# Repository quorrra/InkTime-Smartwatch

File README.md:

# InkTime — Open Source Smartwatch

InkTime is a low-cost, open-source smartwatch designed for extreme battery life and hackability.  
It features a **1.54" E-Paper display**, a **Nordic nRF52840 BLE SoC**, and a high-efficiency power system.

---

## 1) Block Diagram

The hardware architecture revolves around the nRF52840 MCU and a power system designed for month-long battery life.

````text
[ USB Type-C ]                              [ LiPo Battery (250mAh) ]
                 | 5V VBUS                                      |
                 v                                              |
          +---------------+                                     |
          |    BQ25180    | BAT                                 |
          | (Charger IC)  |<------------------------------------+
          +---------------+                                     v
                 | VSYS                                 +---------------+
                 v                                      |   MAX17048    |
          +---------------+                             | (Fuel Gauge)  |
          |    RT6160     |                             +---------------+
          | (Buck-Boost)  |                                     ^
          +---------------+                                     |
                 | 3.3V System Rail (VDD_3V3)                   |
                 |                                              |
 +---------------+----------------------------------------------+-----+
 |               |                                              |     |
 |               v                                              |     |
 |        +-------------+         I2C Bus                       |     |
 |        |  nRF52840   |<======================================+     |
 |        |    MCU      |                                             |
 |        |             |=== I2C ===> [ BMA423 Accelerometer ]        |
 |        |             |=== I2C ===> [ DRV2605L Driver ]-->[ Motor ] |
 |        |             |=== SPI ===> [ 1.54" E-paper Display ]       |
 |        |             |                       ^                      |
 |        |             |-- GPIO (Gate)         | VEPD (Switched Pwr) |
 |        +-------------+      |                |                      |
 |          ^  ^  ^  |         v                |                      |
 |          |  |  |  | +---------------+        |                      |
 +---------(|--|--|)-+-|  PFET Switch  |--------+                      |
            |  |  |  | +---------------+                               |
 [Up]-------+  |  |  |                                                 |
           [Down] |  +--- [ 2.4GHz Antenna ] - - BLE - - [ Companion Phone ]
                  |
              [Enter/Esc]
````

---

## 2) Bill of Materials (BOM)

All components are selected from the JLC Parts library for easy manufacturing and assembly.

| RefDes | Component      | Description               | JLC Part # | Datasheet |
|--------|----------------|---------------------------|------------|-----------|
| U1     | nRF52840       | BLE SoC, Cortex-M4F       | [C137156](https://jlcpcb.com/partdetail/C190794)    | BLE, Native USB      |
| IC1    | BQ25180        | Li-Ion Charger            | [C2907455](https://jlcpcb.com/partdetail/C3682423)   |Safe USB power-path     |
| IC9    | RT6160AWSC     | Buck-Boost Converter      | [C2834376](https://jlcpcb.com/partdetail/C7065276)   | 3.3V System Rail      |
| U3     | MAX17048G      | I2C Fuel Gauge            | [C146603](https://jlcpcb.com/partdetail/C2682616)    | 1-Cell Battery Monitor      |
| IC3    | BMA423         | 3-axis Accelerometer      | [C224345](https://jlcpcb.com/partdetail/C5242966)    | Embedded pedometer      |
| IC4    | DRV2605YZFR    | Haptic Driver             | [C146312](https://jlcpcb.com/partdetail/C527464)    | For ERM motor     |
| J4     | KH-TYPE-C-16P  | USB-C Connector           | [C319148](https://jlcpcb.com/partdetail/C7528806)    |High-side power switch    |

---

## 3) Hardware Functionality

### 3.1 Power Management System
- The watch is powered by a **250mAh LiPo battery**.
- **Charging:** BQ25180 handles USB charging (5V VBUS) and system power-path management.
- **Regulation:** RT6160 buck-boost ensures a stable **3.3V rail** even when battery voltage drops below 3.3V.
- **Fuel Gauge:** MAX17048 uses ModelGauge for accurate **SoC (%)** via I2C, without a sense resistor.

### 3.2 Processing & Connectivity
The **nRF52840** is the central processor, running BLE for smartphone notifications and controlling peripherals over I2C/SPI.

### 3.3 Display & Haptics
- **E-Paper Display:** 1.54", ultra-low power (0W image retention), controlled via SPI.
- **Haptics:** DRV2605 drives an LRA motor for tactile alerts and alarms.

---

## 4) nRF52840 Pin Mapping

| Pin   | Signal Name | Interface  | Function |
|-------|-------------|------------|----------|
| P0.13 | SW_UP       | GPIO (In)  | Up navigation button |
| P0.14 | SW_ENT      | GPIO (In)  | Enter/Select button |
| P1.02 | SW_DN       | GPIO (In)  | Down navigation button |
| P0.08 | I2C_SDA     | I2C Data   | Shared SDA (IMU, Charger, Gauge, Haptic) |
| P1.09 | I2C_SCL     | I2C Clock  | Shared SCL (IMU, Charger, Gauge, Haptic) |
| P0.20 | EPD_RESET   | GPIO (Out) | Display hardware reset |
| P0.22 | EPD_BUSY    | GPIO (In)  | Display status pin |
| P0.12 | HAPTIC_EN   | GPIO (Out) | Enable for DRV2605 haptic driver |
| P0.01 | EPD_DC      | GPIO (Out) | Data/Command selector for E-paper |
| P0.03 | EPD_CS      | SPI CS     | Chip select for E-paper display |

---

## 5) Design & Manufacturing Details

### 5.1 PCB Stackup & Constraints
- **Stackup:** 4-layer PCB (Top, GND Plane, Power Plane, Bottom)
- **Thickness:** 1.0 mm (wearable-friendly)
- **Antenna:** 2.4 GHz PCB antenna at board edge with ground clearance for BLE performance

### 5.2 Component Selection
- **Passives:**  
  - Resistors: 0201 SMD  
  - Capacitors ≤100nF: 0201  
  - Capacitors >100nF: 0402 (unless otherwise specified)
- **Placement:** All components on TOP layer

### 5.3 Routing Rules
- **Power traces** (VCC, VUSB, VBUS, 3V3): 0.3 mm
- **Signal traces:** minimum 0.15 mm
- **Grounding:** solid Layer 2 GND plane + via stitching for EMI/thermal performance

---

## 6) Design Log & Decisions

- **4-layer decision:** moved from 2 to 4 layers to route the 24-pin E-paper connector.
- **GND plane:** Layer 2 kept continuous for RF reference and improved signal integrity.
- **Mechanical fit:** verified in 3D enclosure model (USB-C and buttons aligned with housing).

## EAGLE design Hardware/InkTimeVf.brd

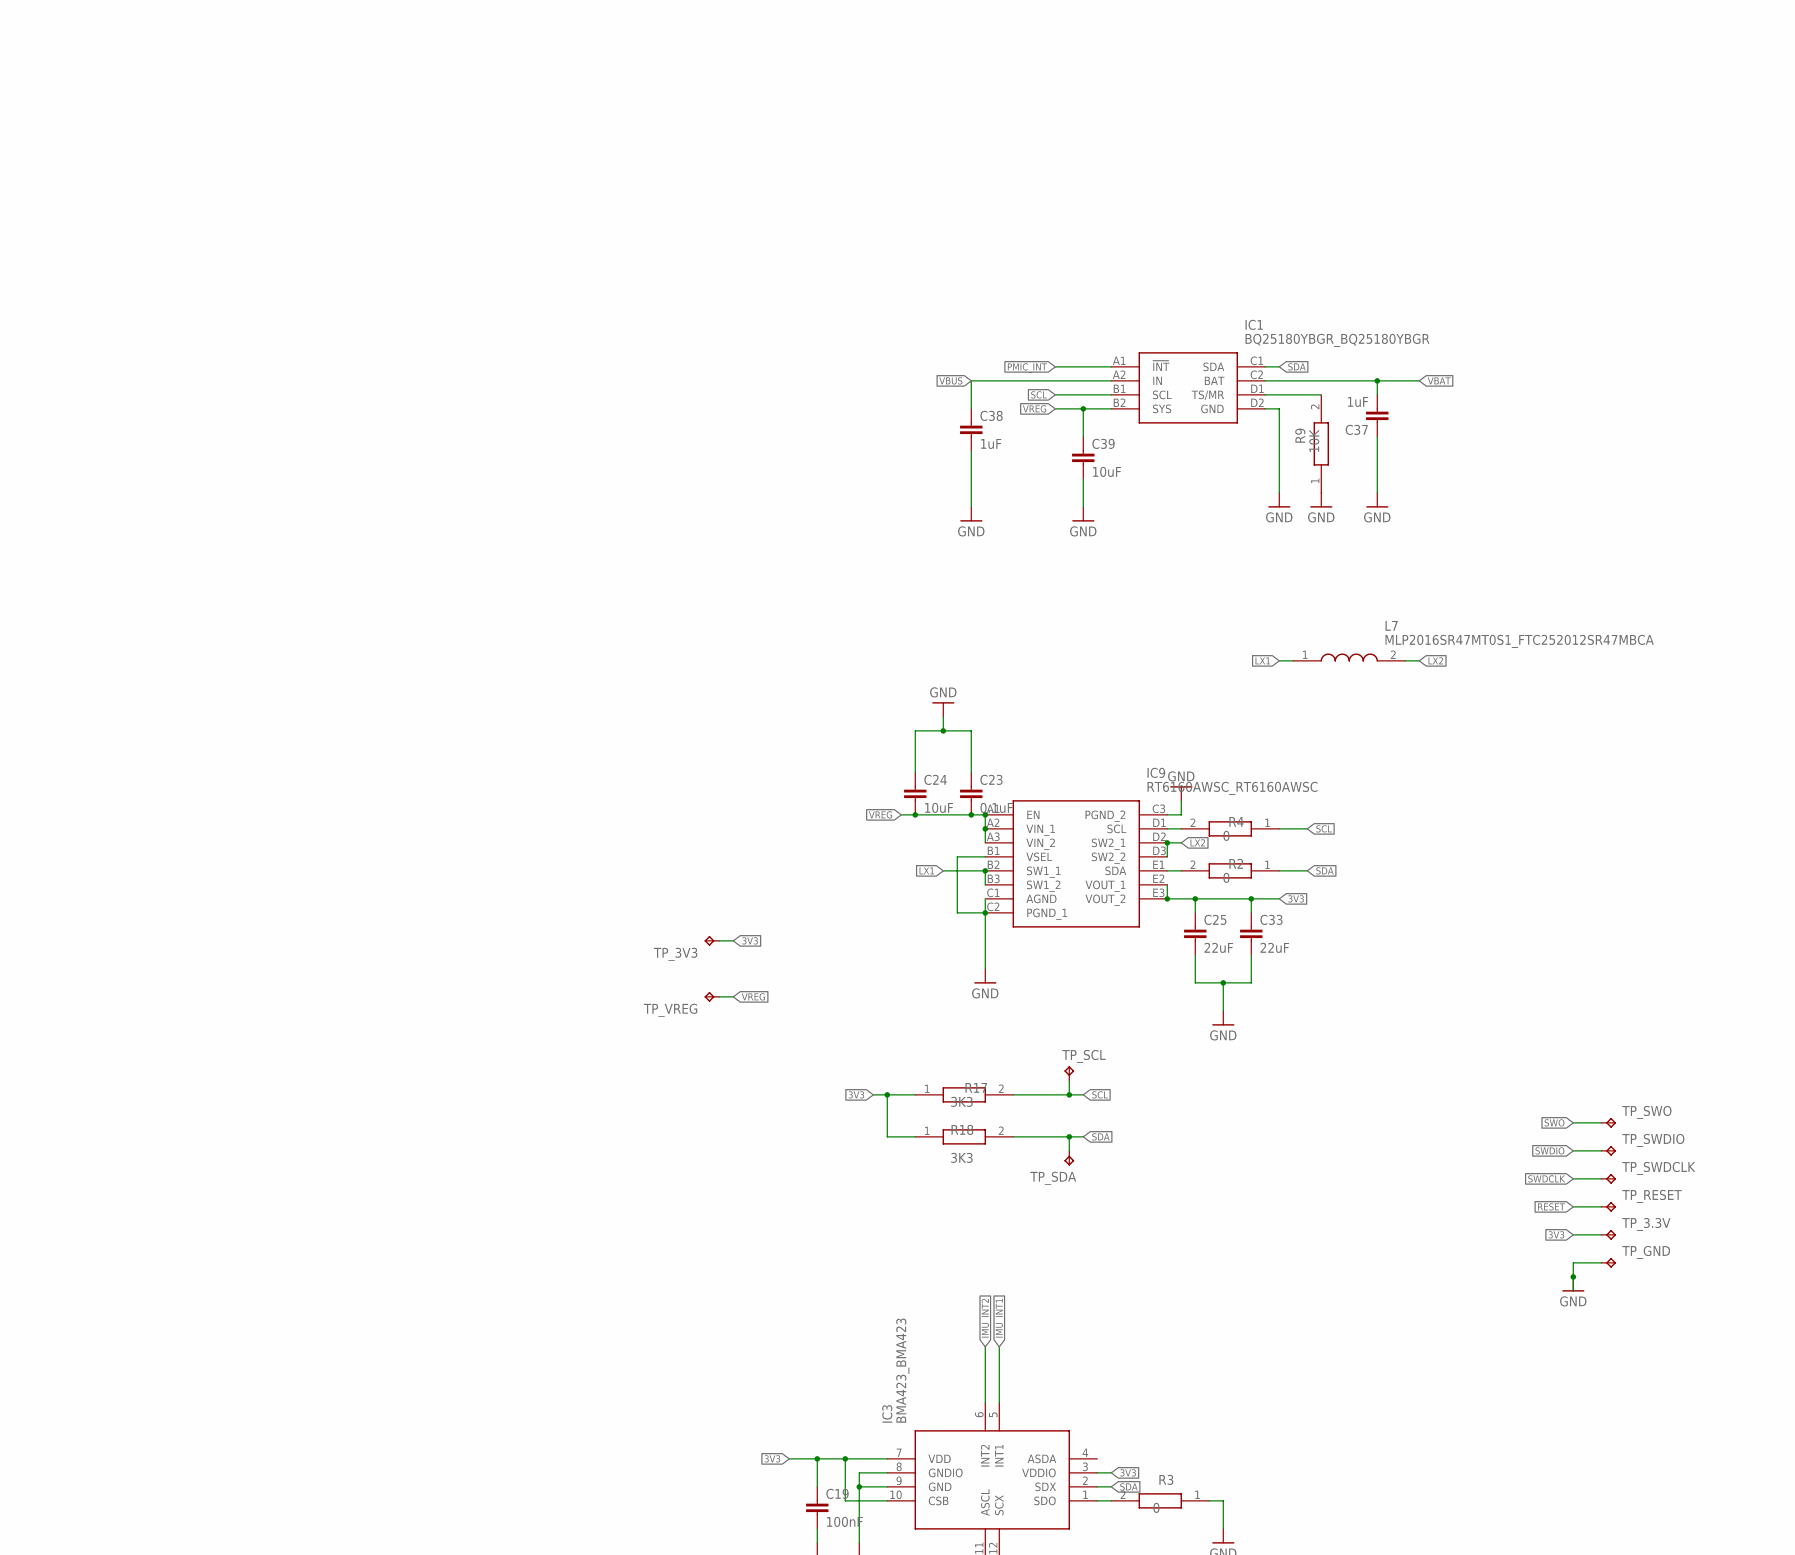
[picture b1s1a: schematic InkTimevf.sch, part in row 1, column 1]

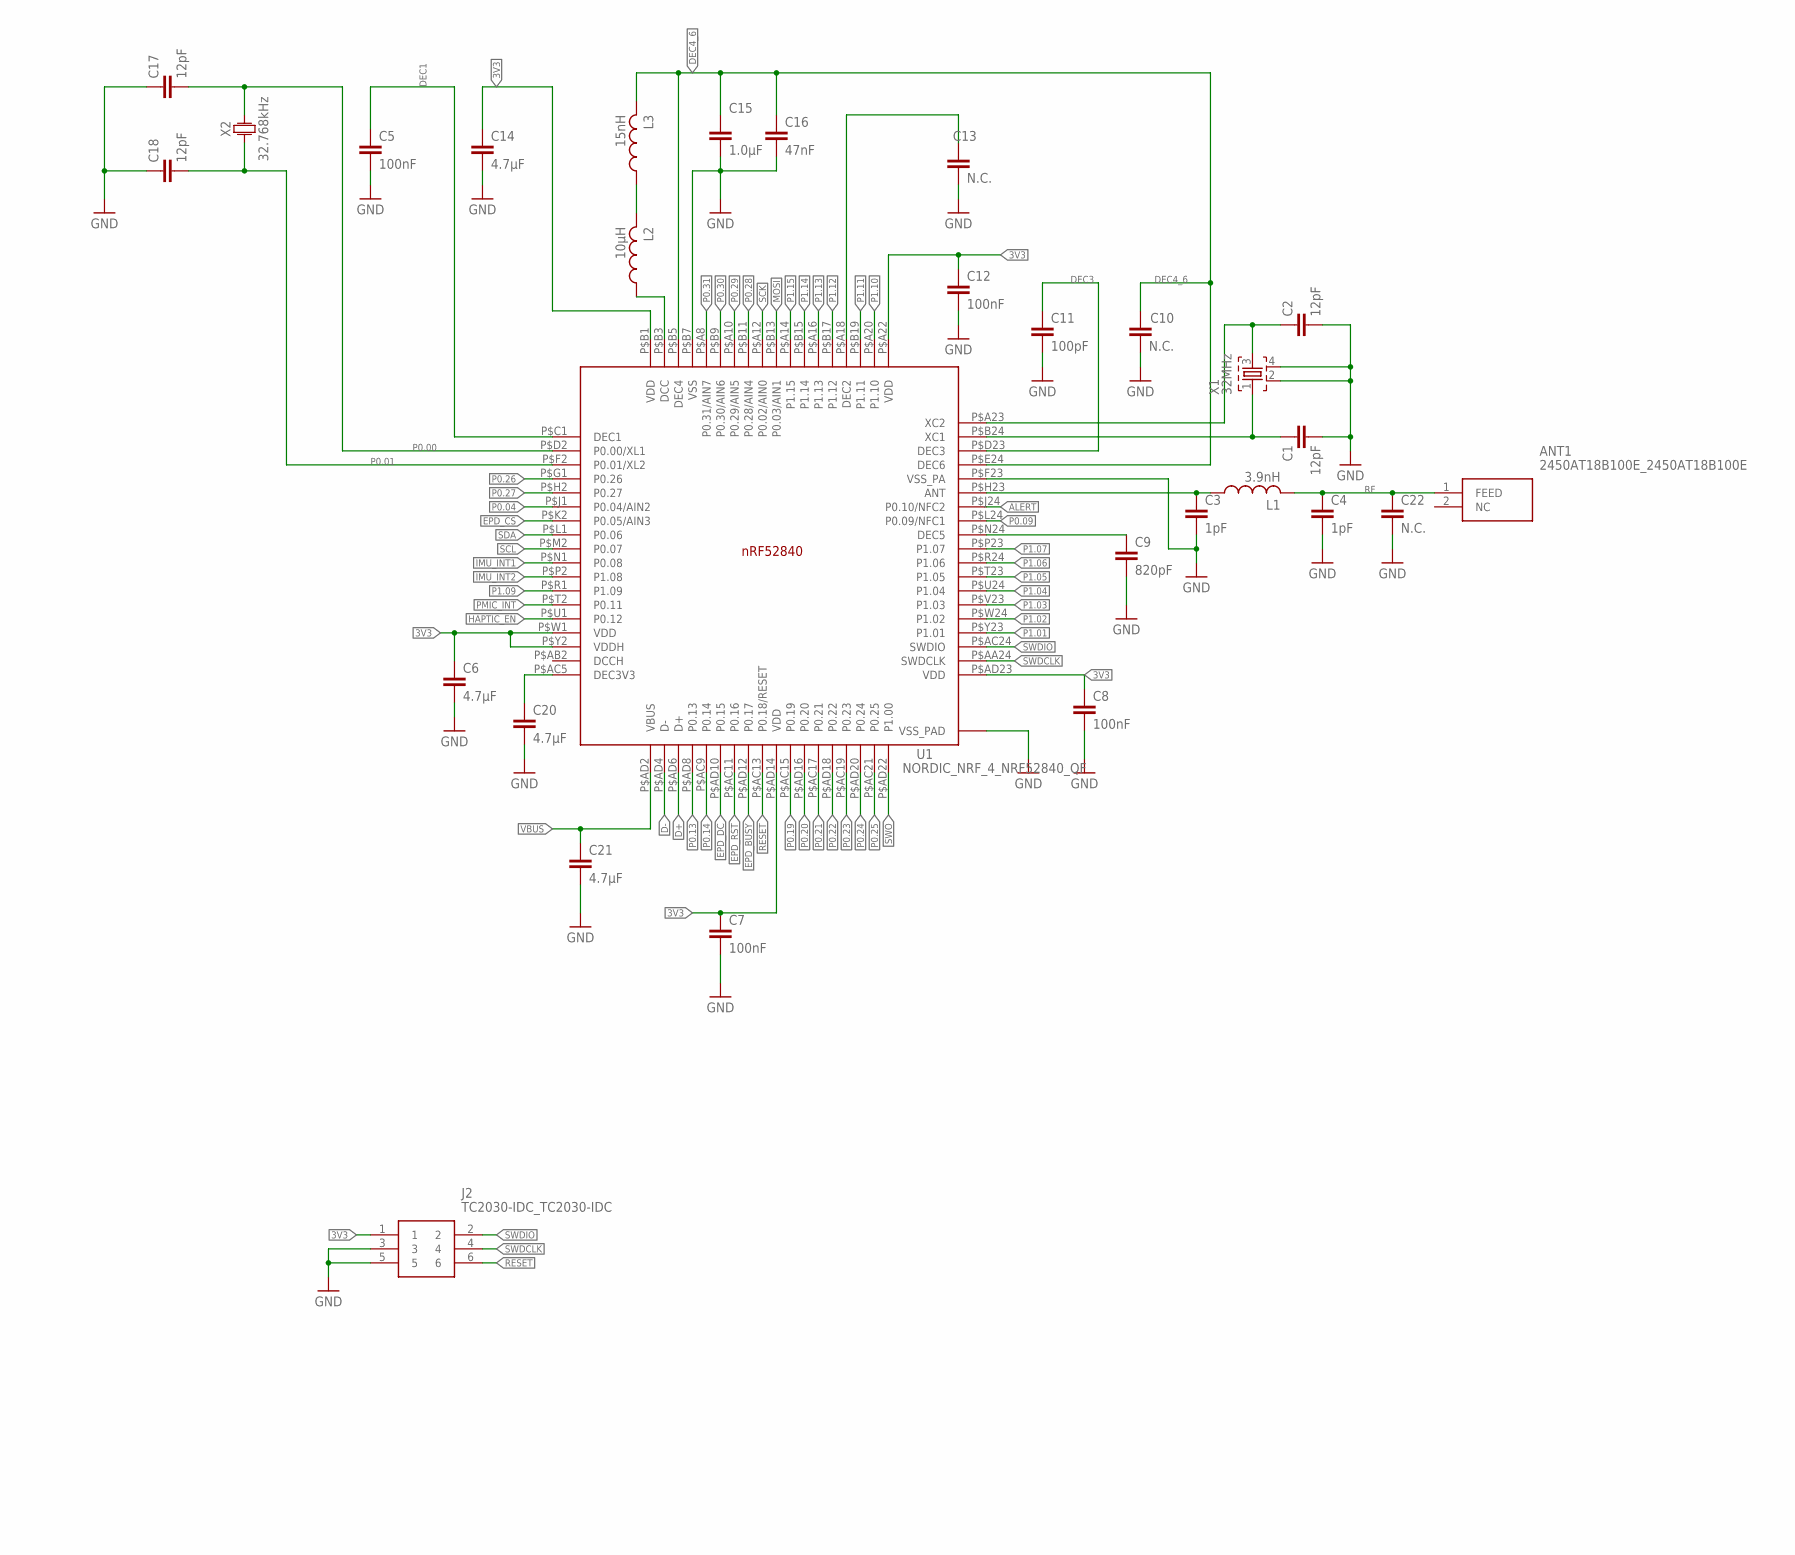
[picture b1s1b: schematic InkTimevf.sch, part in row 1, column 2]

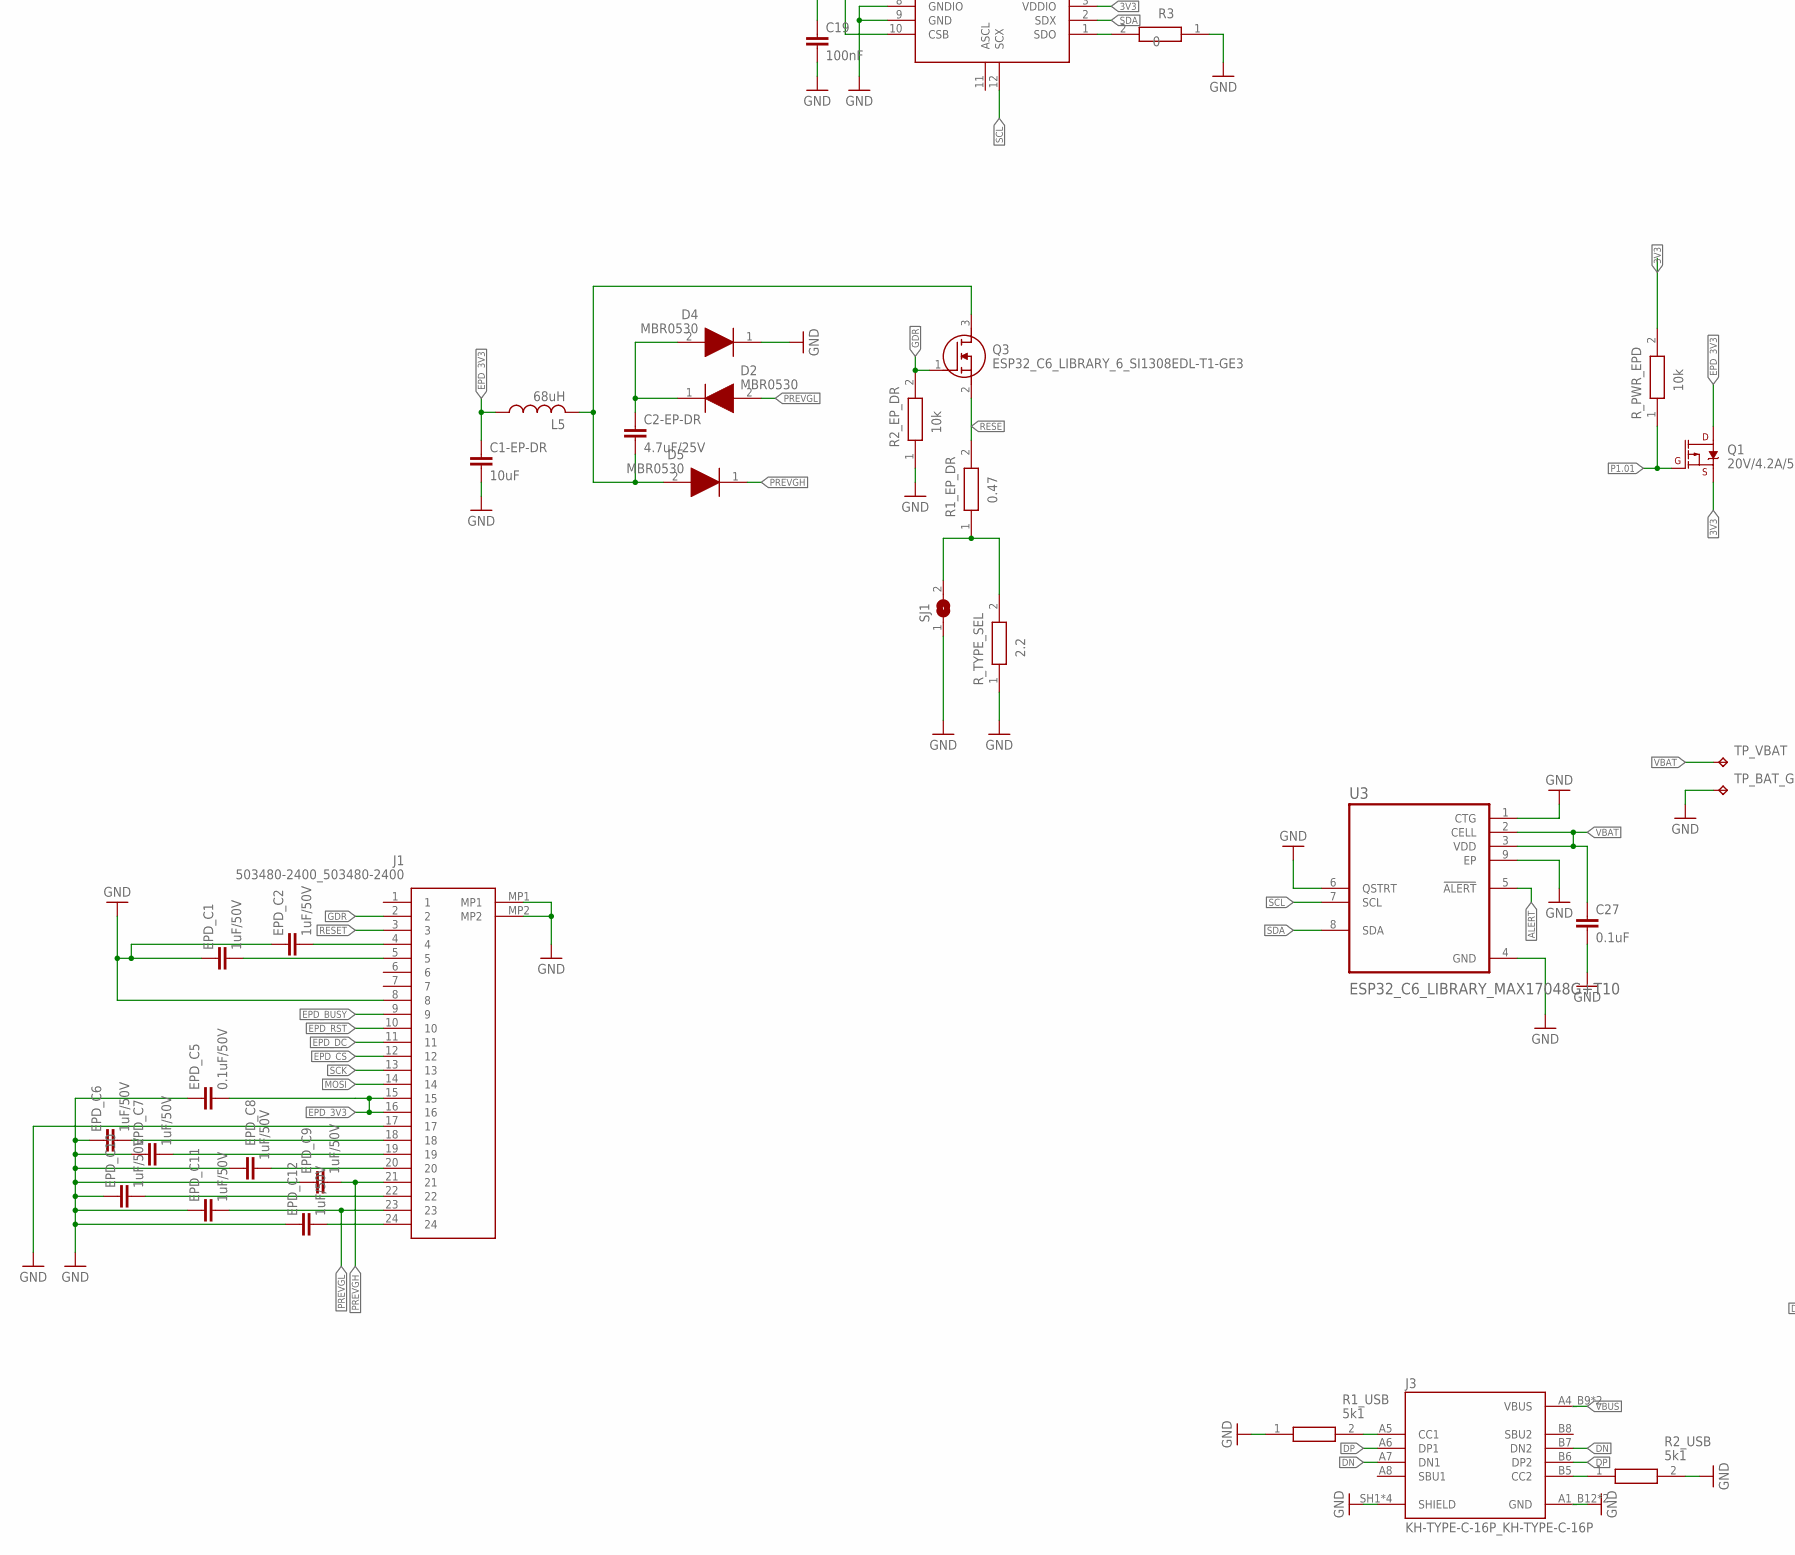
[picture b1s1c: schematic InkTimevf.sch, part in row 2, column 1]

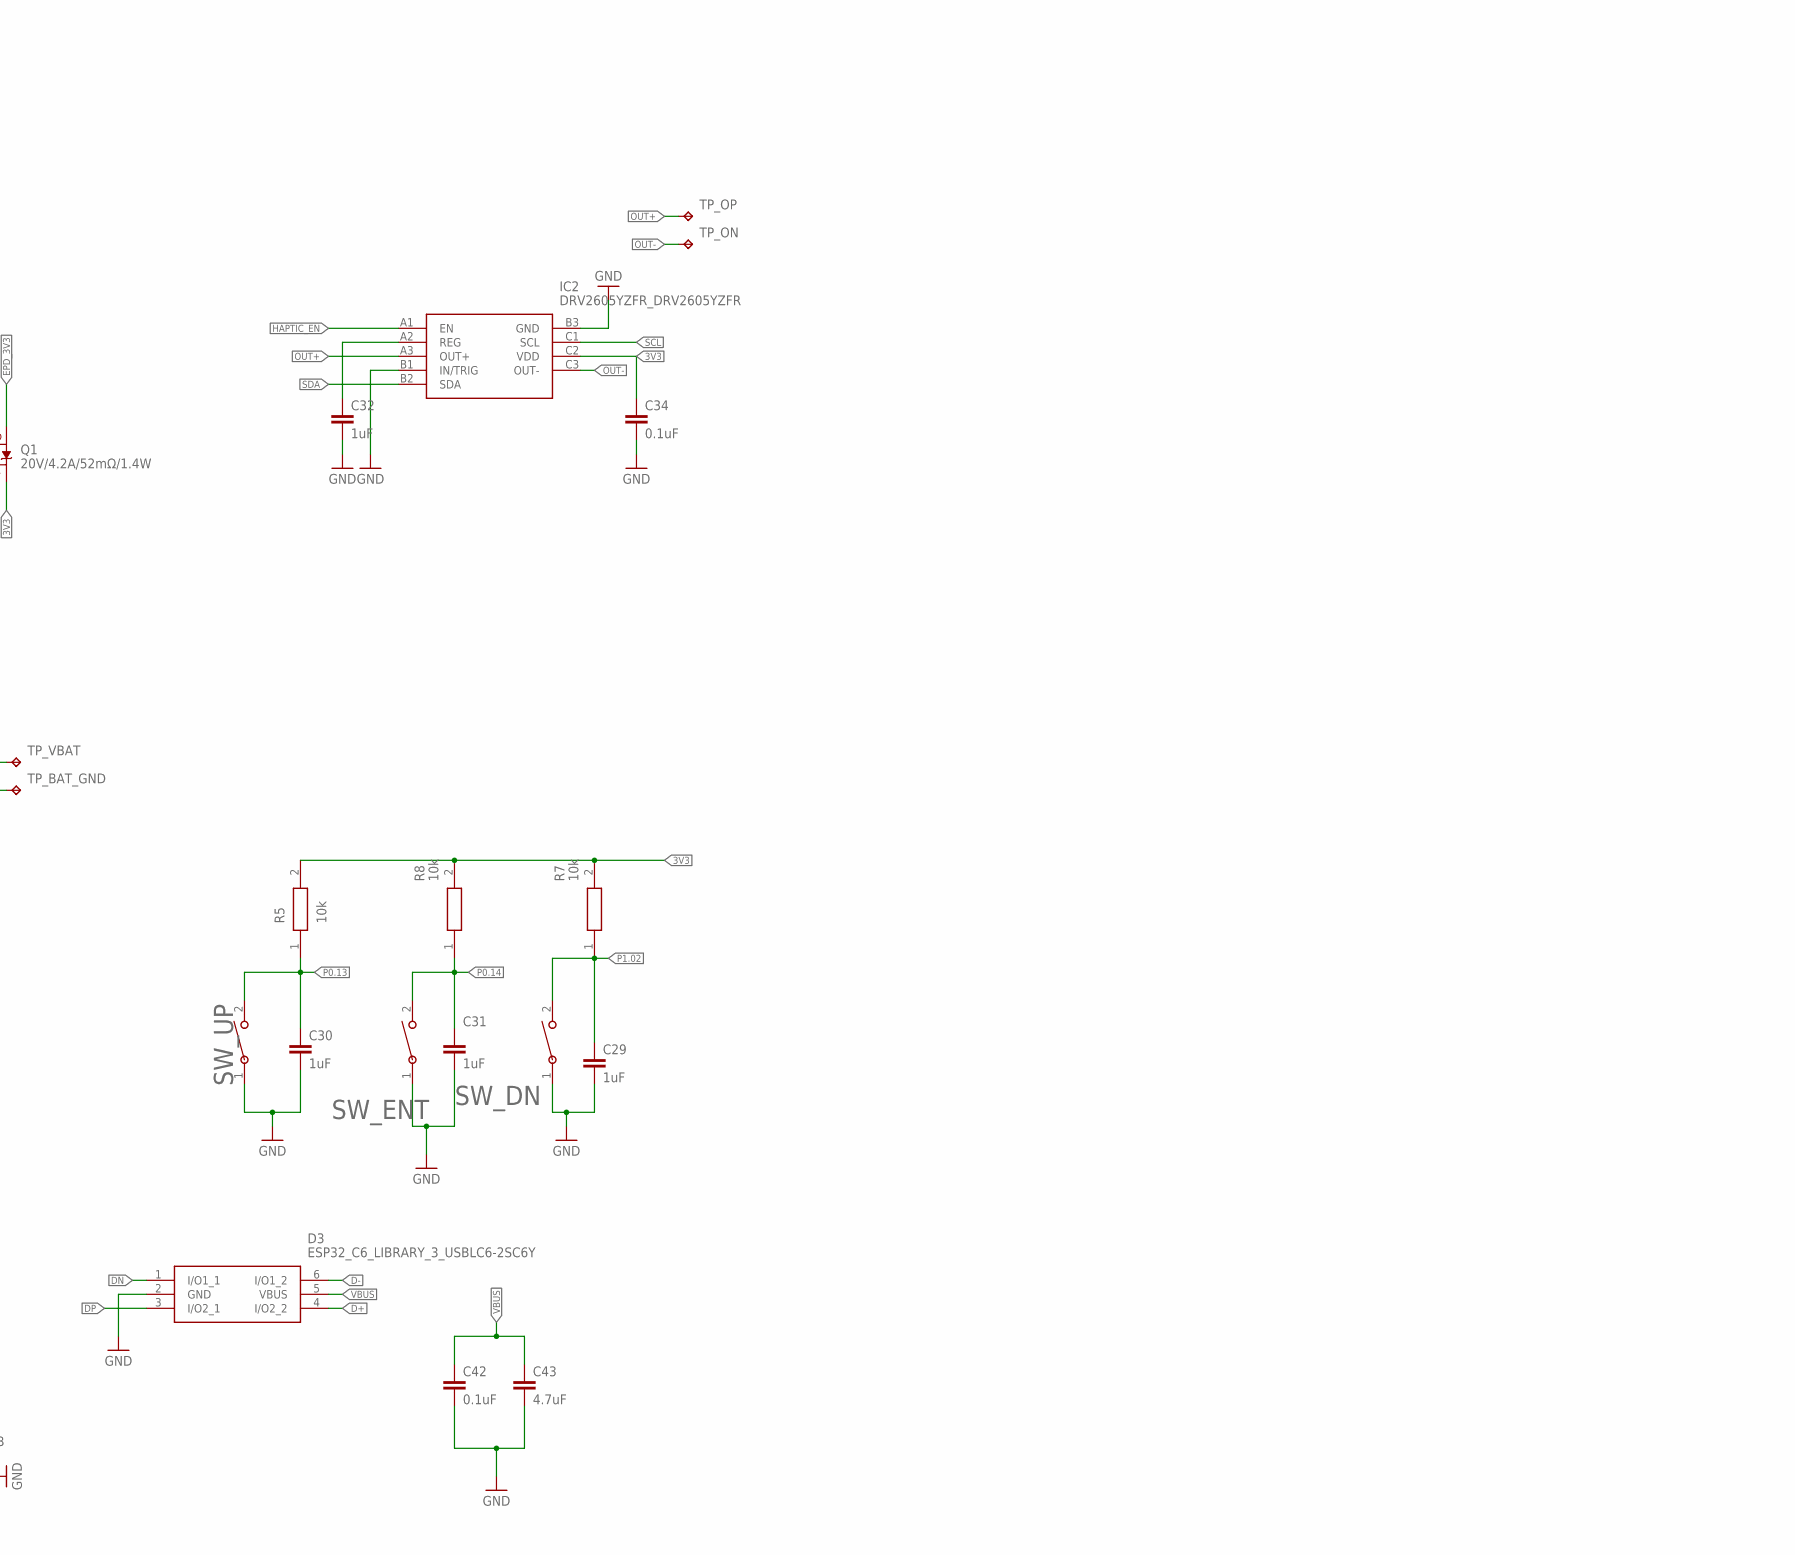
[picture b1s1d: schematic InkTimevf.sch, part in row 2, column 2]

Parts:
ANT1: 2450AT18B100E_2450AT18B100E; 2450AT18B100E_ANTC3216X140N
C1, C2, C17, C18: 12pF; NORDIC_NRF_3_RESC0201_L
C1-EP-DR, C24, C39: 10uF; ESP32_C6_LIBRARY_1_ESP32_WROVER_EAGLE-LTSPICE_C0402
C2-EP-DR: 4.7uF/25V; ESP32_C6_LIBRARY_1_ESP32_WROVER_EAGLE-LTSPICE_C0402
C3, C4: 1pF; NORDIC_NRF_3_RESC0201_L
C5, C7, C8, C12, C19: 100nF; NORDIC_NRF_3_RESC0201_L
C6, C14, C20, C21: 4.7µF; ESP32_C6_LIBRARY_1_ESP32_WROVER_EAGLE-LTSPICE_C0402
C9: 820pF; NORDIC_NRF_3_RESC0201_L
C10, C13, C22: N.C.; NORDIC_NRF_3_RESC0201_L
C11: 100pF; NORDIC_NRF_3_RESC0201_L
C15: 1.0µF; ESP32_C6_LIBRARY_1_ESP32_WROVER_EAGLE-LTSPICE_C0402
C16: 47nF; NORDIC_NRF_3_RESC0201_L
C23, C27, C34, C42: 0.1uF; NORDIC_NRF_3_RESC0201_L
C25, C33: 22uF; ESP32_C6_LIBRARY_1_ESP32_WROVER_EAGLE-LTSPICE_C0402
C29, C30, C31, C32, C37, C38: 1uF; ESP32_C6_LIBRARY_1_ESP32_WROVER_EAGLE-LTSPICE_C0402
C43: 4.7uF; ESP32_C6_LIBRARY_1_ESP32_WROVER_EAGLE-LTSPICE_C0402
D2, D4, D5: MBR0530; ESP32_C6_LIBRARY_5_SOD3716X135N
D3: ESP32_C6_LIBRARY_3_USBLC6-2SC6Y; ESP32_C6_LIBRARY_3_SOT95P280X145-6N
EPD_C1, EPD_C2, EPD_C6, EPD_C7, EPD_C8, EPD_C9, EPD_C10, EPD_C11, EPD_C12: 1uF/50V; ESP32_C6_LIBRARY_1_ESP32_WROVER_EAGLE-LTSPICE_C0402
EPD_C5: 0.1uF/50V; NORDIC_NRF_3_RESC0201_L
IC1: BQ25180YBGR_BQ25180YBGR; BQ25180YBGR_BGA8C40P2X4_100X155X50
IC2: DRV2605YZFR_DRV2605YZFR; DRV2605YZFR_BGA9C50P3X3_144X144X62
IC3: BMA423_BMA423
IC9: RT6160AWSC_RT6160AWSC; RT6160AWSC_BGA15C40P3X5_140X230X60
J1: 503480-2400_503480-2400; 503480-2400_5034802400
J2: TC2030-IDC_TC2030-IDC; TC2030-IDC_TC2030IDC
J3: KH-TYPE-C-16P_KH-TYPE-C-16P; KH-TYPE-C-16P_KINGHELM_KH-TYPE-C-16P
L1: 3.9nH; NORDIC_NRF_2_RESC0402_L
L2: 10µH; NORDIC_NRF_2_RESC0402_L
L3: 15nH; NORDIC_NRF_2_RESC0402_L
L5: 68uH; NORDIC_NRF_2_RESC0402_L
L7: MLP2016SR47MT0S1_FTC252012SR47MBCA; MLP2016SR47MT0S1_INDC2016X100N
Q1: 20V/4.2A/52mΩ/1.4W; ESP32_C6_LIBRARY_4_ESP32_C6_LIBRARY_4_ESP32_C6_LIBRARY_4_ES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
Q3: ESP32_C6_LIBRARY_6_SI1308EDL-T1-GE3; ESP32_C6_LIBRARY_6_SOT65P210X110-3N
R1_EP_DR: 0.47; CPF0201D7K68C1_0201
R1_USB, R2_USB: 5k1; CPF0201D7K68C1_0201
R2, R4: 0; ERA-1AEB3401C_0201
R2_EP_DR, R5, R7, R8: 10k; CPF0201D7K68C1_0201
R3: 0; CPF0201D7K68C1_0201
R9: 10K; CPF0201D7K68C1_0201
R17, R18: 3K3; ERA-1AEB3401C_0201
R_PWR_EPD: 10k; ERA-1AEB3401C_0201
R_TYPE_SEL: 2.2; CPF0201D7K68C1_0201
SJ1: ESP32_C6_LIBRARY_7_JUMPER_SJ
SW_DN: 2025-10-22_07-23-44_LIBRARY_EVP-AKE31ASW_EVP-AKE3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; 2025-10-22_07-23-44_LIBRARY_SW_EVP-AKE31A_PAN
SW_ENT: 2025-10-22_07-23-44_LIBRARY_EVP-AKE31ASW_EVP-AKE3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; 2025-10-22_07-23-44_LIBRARY_SW_EVP-AKE31A_PAN
SW_UP: 2025-10-22_07-23-44_LIBRARY_EVP-AKE31ASW_EVP-AKE3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; 2025-10-22_07-23-44_LIBRARY_SW_EVP-AKE31A_PAN
TP_3.3V, TP_3V3: HECTOR_WATCH_1_TPTP20R; HECTOR_WATCH_1_TP20R
TP_BAT_GND: HECTOR_WATCH_1_TPTP20R; HECTOR_WATCH_1_TP20R
TP_GND: HECTOR_WATCH_1_TPTP20R; HECTOR_WATCH_1_TP20R
TP_ON: HECTOR_WATCH_1_TPTP20R; HECTOR_WATCH_1_TP20R
TP_OP: HECTOR_WATCH_1_TPTP20R; HECTOR_WATCH_1_TP20R
TP_RESET: HECTOR_WATCH_1_TPTP20R; HECTOR_WATCH_1_TP20R
TP_SCL: HECTOR_WATCH_1_TPTP20R; HECTOR_WATCH_1_TP20R
TP_SDA: HECTOR_WATCH_1_TPTP20R; HECTOR_WATCH_1_TP20R
TP_SWDCLK: HECTOR_WATCH_1_TPTP20R; HECTOR_WATCH_1_TP20R
TP_SWDIO: HECTOR_WATCH_1_TPTP20R; HECTOR_WATCH_1_TP20R
TP_SWO: HECTOR_WATCH_1_TPTP20R; HECTOR_WATCH_1_TP20R
TP_VBAT: HECTOR_WATCH_1_TPTP20R; HECTOR_WATCH_1_TP20R
TP_VREG: HECTOR_WATCH_1_TPTP20R; HECTOR_WATCH_1_TP20R
U1: NORDIC_NRF_4_NRF52840_QF; NORDIC_NRF_4_AQFN50P700X700X85_HS-74N
U3: ESP32_C6_LIBRARY_MAX17048G+T10; ESP32_C6_LIBRARY_SON50P200X200X80-9N
X1: 32MHz; NORDIC_NRF_BT-XTAL_2016_N
X2: 32.768kHz; XTAL330X1051X90N

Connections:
3V3: C6.1, C7.1, C8.1, C12.1, C14.1, C19.1, C25.1, C33.1, C34.1, IC2.C2 (VDD), IC3.3 (VDDIO), IC3.7 (VDD), IC3.10 (CSB), IC9.E2 (VOUT_1), IC9.E3 (VOUT_2), J2.1, Q1.2 (S), R5.2, R7.2, R8.2, R17.1, R18.1, R_PWR_EPD.2, TP_3.3V.TP, TP_3V3.TP, U1.P$A22 (VDD), U1.P$AD14 (VDD), U1.P$AD23 (VDD), U1.P$B1 (VDD), U1.P$W1 (VDD), U1.P$Y2 (VDDH)
ALERT: U1.P$J24 (P0.10/NFC2), U3.5 (!ALERT)
D+: D3.4 (I/O2_2), U1.P$AD6 (D+)
D-: D3.6 (I/O1_2), U1.P$AD4 (D-)
DEC1: C5.1, U1.P$C1 (DEC1)
DEC3: C11.1, U1.P$D23 (DEC3)
DEC4_6: C10.1, C15.1, C16.1, L3.2, U1.P$B5 (DEC4), U1.P$E24 (DEC6)
DN: D3.1 (I/O1_1), J3.A7 (DN1), J3.B7 (DN2)
DP: D3.3 (I/O2_1), J3.A6 (DP1), J3.B6 (DP2)
EPD_3V3: C1-EP-DR.1, EPD_C5.2, J1.15, J1.16, L5.1, Q1.3 (D)
EPD_BUSY: J1.9, U1.P$AD12 (P0.17)
EPD_CS: J1.12, U1.P$K2 (P0.05/AIN3)
EPD_DC: J1.11, U1.P$AD10 (P0.15)
EPD_RST: J1.10, U1.P$AC11 (P0.16)
GDR: J1.2, Q3.1 (G), R2_EP_DR.2
GND: C1.2, C1-EP-DR.2, C2.2, C3.2, C4.2, C5.2, C6.2, C7.2, C8.2, C9.2, C10.2, C11.2, C12.2, C13.2, C14.2, C15.2, C16.2, C17.1, C18.1, C19.2, C20.2, C21.2, C22.2, C23.1, C24.1, C25.2, C27.2, C29.2, C30.2, C31.2, C32.2, C33.2, C34.2, C37.1, C38.2, C39.2, C42.2, C43.2, D3.2 (GND), D4.1 (K), EPD_C1.1, EPD_C2.1, EPD_C5.1, EPD_C6.1, EPD_C7.1, EPD_C8.1, EPD_C9.1, EPD_C10.1, EPD_C11.1, EPD_C12.1, IC1.D2 (GND), IC2.B1 (IN/TRIG), IC2.B3 (GND), IC3.8 (GNDIO), IC3.9 (GND), IC9.B1 (VSEL), IC9.C1 (AGND), IC9.C2 (PGND_1), IC9.C3 (PGND_2), J1.8, J1.17, J1.MP1, J1.MP2, J2.3, J2.5, J3.A1_B12 (GND), J3.A12_B1 (GND), J3.SH1 (SHIELD), J3.SH2 (SHIELD), J3.SH3 (SHIELD), J3.SH4 (SHIELD), R1_USB.1, R2_EP_DR.1, R2_USB.2, R3.1, R9.1, R_TYPE_SEL.1, SJ1.1, SW_DN.1, SW_ENT.1, SW_UP.1, TP_BAT_GND.TP, TP_GND.TP, U1.P$74 (VSS_PAD), U1.P$75 (VSS_PAD), U1.P$76 (VSS_PAD), U1.P$77 (VSS_PAD), U1.P$78 (VSS_PAD), U1.P$79 (VSS_PAD), U1.P$80 (VSS_PAD), U1.P$81 (VSS_PAD), U1.P$82 (VSS_PAD), U1.P$83 (VSS_PAD), U1.P$84 (VSS_PAD), U1.P$85 (VSS_PAD), U1.P$86 (VSS_PAD), U1.P$87 (VSS_PAD), U1.P$88 (VSS_PAD), U1.P$89 (VSS_PAD), U1.P$90 (VSS_PAD), U1.P$B7 (VSS), U1.P$F23 (VSS_PA), U3.1 (CTG), U3.4 (GND), U3.6 (QSTRT), U3.9 (EP), X1.2, X1.4
HAPTIC_EN: IC2.A1 (EN), U1.P$U1 (P0.12)
IMU_INT1: IC3.5 (INT1), U1.P$N1 (P0.08)
IMU_INT2: IC3.6 (INT2), U1.P$P2 (P1.08)
LX1: IC9.B2 (SW1_1), IC9.B3 (SW1_2), L7.1
LX2: IC9.D2 (SW2_1), IC9.D3 (SW2_2), L7.2
MOSI: J1.14, U1.P$B13 (P0.03/AIN1)
unnamed: IC1.D1 (TS/MR), R9.2
unnamed: C3.1, L1.1, U1.P$H23 (ANT)
unnamed: L2.2, L3.1
unnamed: IC9.D1 (SCL), R4.2
unnamed: C1.1, U1.P$B24 (XC1), X1.1
unnamed: C2.1, U1.P$A23 (XC2), X1.3
unnamed: IC9.E1 (SDA), R2.2
unnamed: C20.1, U1.P$AC5 (DEC3V3)
unnamed: C2-EP-DR.2, D5.2 (A), L5.2, Q3.3 (D)
unnamed: C9.1, U1.P$N24 (DEC5)
unnamed: C13.1, U1.P$A18 (DEC2)
unnamed: EPD_C7.2, J1.19
unnamed: C2-EP-DR.1, D2.1 (K), D4.2 (A)
unnamed: R1_EP_DR.1, R_TYPE_SEL.2, SJ1.2
unnamed: IC3.1 (SDO), R3.2
unnamed: C32.1, IC2.A2 (REG)
unnamed: EPD_C2.2, J1.4
unnamed: EPD_C1.2, J1.5
unnamed: L2.1, U1.P$B3 (DCC)
unnamed: EPD_C6.2, J1.18
unnamed: EPD_C8.2, J1.20
unnamed: EPD_C10.2, J1.22
unnamed: EPD_C12.2, J1.24
unnamed: J3.B5 (CC2), R2_USB.1
unnamed: J3.A5 (CC1), R1_USB.2
OUT+: IC2.A3 (OUT+), TP_OP.TP
OUT-: IC2.C3 (OUT-), TP_ON.TP
P0.00: C17.2, U1.P$D2 (P0.00/XL1), X2.2
P0.01: C18.2, U1.P$F2 (P0.01/XL2), X2.1
P0.04: U1.P$J1 (P0.04/AIN2)
P0.09: U1.P$L24 (P0.09/NFC1)
P0.13: C30.1, R5.1, SW_UP.2, U1.P$AD8 (P0.13)
P0.14: C31.1, R8.1, SW_ENT.2, U1.P$AC9 (P0.14)
P0.19: U1.P$AC15 (P0.19)
P0.20: U1.P$AD16 (P0.20)
P0.21: U1.P$AC17 (P0.21)
P0.22: U1.P$AD18 (P0.22)
P0.23: U1.P$AC19 (P0.23)
P0.24: U1.P$AD20 (P0.24)
P0.25: U1.P$AC21 (P0.25)
P0.26: U1.P$G1 (P0.26)
P0.27: U1.P$H2 (P0.27)
P0.28: U1.P$B11 (P0.28/AIN4)
P0.29: U1.P$A10 (P0.29/AIN5)
P0.30: U1.P$B9 (P0.30/AIN6)
P0.31: U1.P$A8 (P0.31/AIN7)
P1.01: Q1.1 (G), R_PWR_EPD.1, U1.P$Y23 (P1.01)
P1.02: C29.1, R7.1, SW_DN.2, U1.P$W24 (P1.02)
P1.03: U1.P$V23 (P1.03)
P1.04: U1.P$U24 (P1.04)
P1.05: U1.P$T23 (P1.05)
P1.06: U1.P$R24 (P1.06)
P1.07: U1.P$P23 (P1.07)
P1.09: U1.P$R1 (P1.09)
P1.10: U1.P$A20 (P1.10)
P1.11: U1.P$B19 (P1.11)
P1.12: U1.P$B17 (P1.12)
P1.13: U1.P$A16 (P1.13)
P1.14: U1.P$B15 (P1.14)
P1.15: U1.P$A14 (P1.15)
PMIC_INT: IC1.A1 (!INT), U1.P$T2 (P0.11)
PREVGH: D5.1 (K), EPD_C9.2, J1.21
PREVGL: D2.2 (A), EPD_C11.2, J1.23
RESE: Q3.2 (S), R1_EP_DR.2
RESET: J1.3, J2.6, TP_RESET.TP, U1.P$AC13 (P0.18/RESET)
RF: ANT1.1 (FEED), C4.1, C22.1, L1.2
SCK: J1.13, U1.P$A12 (P0.02/AIN0)
SCL: IC1.B1 (SCL), IC2.C1 (SCL), IC3.12 (SCX), R4.1, R17.2, TP_SCL.TP, U1.P$M2 (P0.07), U3.7 (SCL)
SDA: IC1.C1 (SDA), IC2.B2 (SDA), IC3.2 (SDX), R2.1, R18.2, TP_SDA.TP, U1.P$L1 (P0.06), U3.8 (SDA)
SWDCLK: J2.4, TP_SWDCLK.TP, U1.P$AA24 (SWDCLK)
SWDIO: J2.2, TP_SWDIO.TP, U1.P$AC24 (SWDIO)
SWO: TP_SWO.TP, U1.P$AD22 (P1.00)
VBAT: C27.1, C37.2, IC1.C2 (BAT), TP_VBAT.TP, U3.2 (CELL), U3.3 (VDD)
VBUS: C21.1, C38.1, C42.1, C43.1, D3.5 (VBUS), IC1.A2 (IN), J3.A4_B9 (VBUS), J3.A9_B4 (VBUS), U1.P$AD2 (VBUS)
VREG: C23.2, C24.2, C39.1, IC1.B2 (SYS), IC9.A1 (EN), IC9.A2 (VIN_1), IC9.A3 (VIN_2), TP_VREG.TP

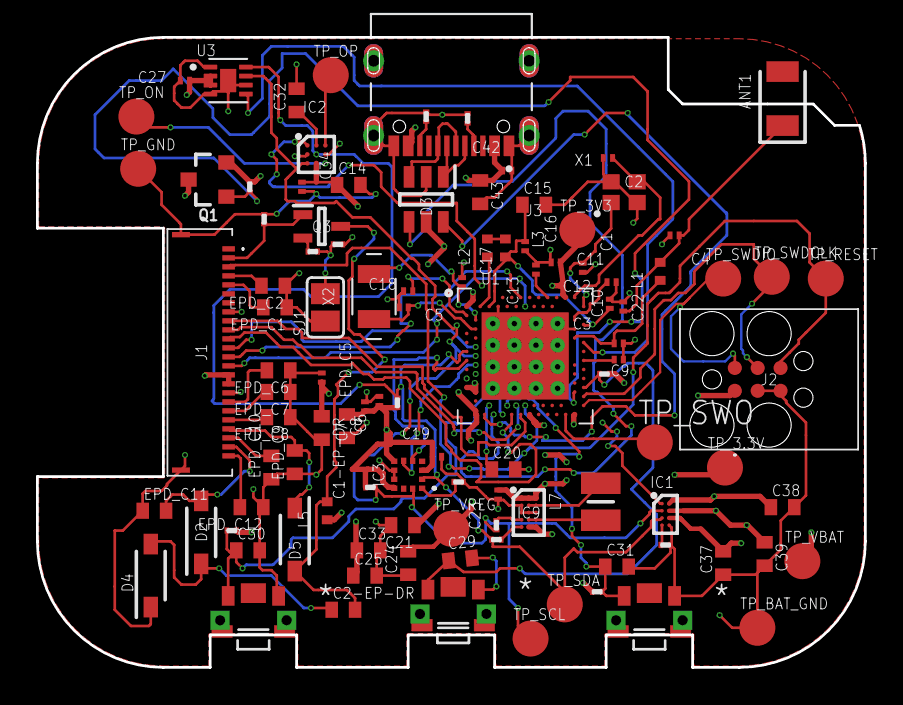
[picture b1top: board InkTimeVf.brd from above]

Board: 4 copper layers, 46.0 x 35.0 mm, 105 parts (0 on the bottom side), 70 nets.

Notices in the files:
parts and their libraries:
COPYRIGHT: Copyright (C) 2025 Ultra Librarian. All rights reserved.
